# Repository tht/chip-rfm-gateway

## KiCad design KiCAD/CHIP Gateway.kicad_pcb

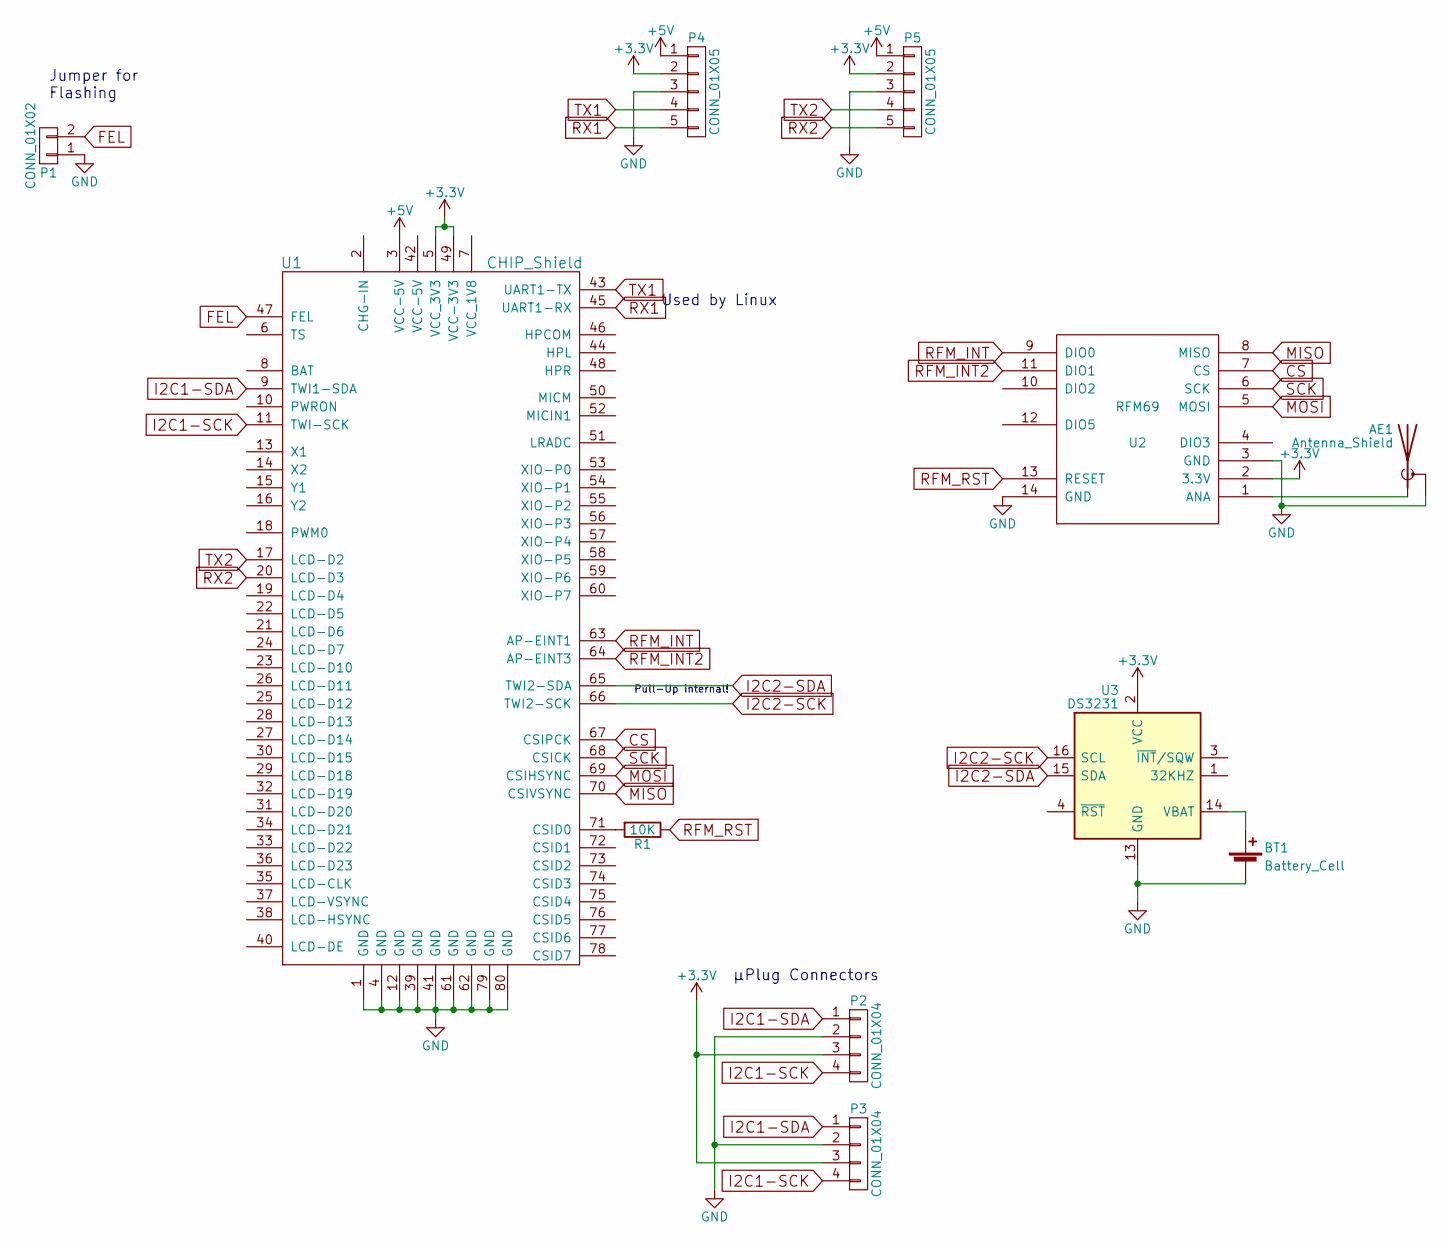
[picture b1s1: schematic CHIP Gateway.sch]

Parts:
AE1: Antenna_Shield; U.FL-COAX
BT1: Battery_Cell; CR2032_SLIDE
P1: CONN_01X02; Pin_Header_Straight_1x02_Pitch2.54mm
P2, P3: CONN_01X04; Pin_Header_Straight_1x04_Pitch2.54mm
P4, P5: CONN_01X05; JST_XH_S05B-XH-A_05x2.50mm_Angled
R1: 10K; R_0805_HandSoldering
U1: CHIP_Shield; CHIP
U2: RFM69; RFM69CW
U3: DS3231; SOIC-16W_7.5x10.3mm_Pitch1.27mm

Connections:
+3V3: P2.3, P3.3, P4.2, P5.2, U1.5 (VCC_3V3), U1.49 (VCC-3V3), U2.2 (3.3V), U3.2 (VCC)
+5V: P4.1, P5.1, U1.3 (VCC-5V)
CS: U1.67 (CSIPCK), U2.7 (CS)
FEL: P1.2, U1.47 (FEL)
GND: AE1.2 (Shield), BT1.2 (-), P1.1, P2.2, P3.2, P4.3, P5.3, U1.1 (GND), U1.4 (GND), U1.12 (GND), U1.39 (GND), U1.41 (GND), U1.61 (GND), U1.62 (GND), U1.79 (GND), U1.80 (GND), U2.3 (GND), U2.14 (GND), U3.5 (NC), U3.6 (NC), U3.7 (NC), U3.8 (NC), U3.9 (NC), U3.10 (NC), U3.11 (NC), U3.12 (NC), U3.13 (GND)
I2C1-SCK: P2.4, P3.4, U1.11 (TWI-SCK)
I2C1-SDA: P2.1, P3.1, U1.9 (TWI1-SDA)
I2C2-SCK: U1.66 (TWI2-SCK), U3.16 (SCL)
I2C2-SDA: U1.65 (TWI2-SDA), U3.15 (SDA)
MISO: U1.70 (CSIVSYNC), U2.8 (MISO)
MOSI: U1.69 (CSIHSYNC), U2.5 (MOSI)
unnamed: AE1.1 (A), U2.1 (ANA)
unnamed: BT1.1 (+), U3.14 (VBAT)
unnamed: R1.2, U1.71 (CSID0)
RFM_INT: U1.63 (AP-EINT1), U2.9 (DIO0)
RFM_INT2: U1.64 (AP-EINT3), U2.11 (DIO1)
RFM_RST: R1.1, U2.13 (RESET)
RX1: P4.5, U1.45 (UART1-RX)
RX2: P5.5, U1.20 (LCD-D3)
SCK: U1.68 (CSICK), U2.6 (SCK)
TX1: P4.4, U1.43 (UART1-TX)
TX2: P5.4, U1.17 (LCD-D2)

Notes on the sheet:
Used by Linux
Jumper for Flashing
µPlug Connectors
Pull-Up internal!

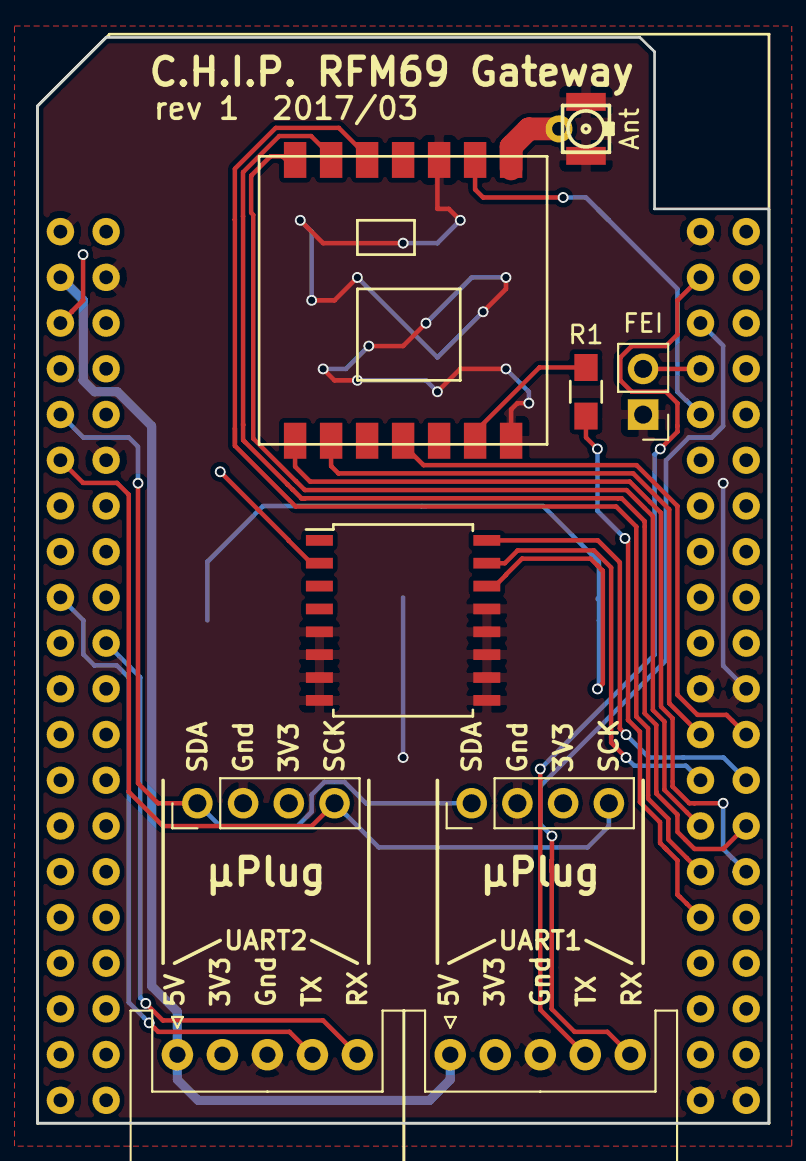
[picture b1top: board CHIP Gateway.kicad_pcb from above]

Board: 2 copper layers, 40.6 x 60.3 mm, 11 parts (1 on the bottom side), 22 nets.

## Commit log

2017-02-19 Ready for ordering
2017-02-19 Connected DIO1
2017-02-26 Rev 1 as ordered
